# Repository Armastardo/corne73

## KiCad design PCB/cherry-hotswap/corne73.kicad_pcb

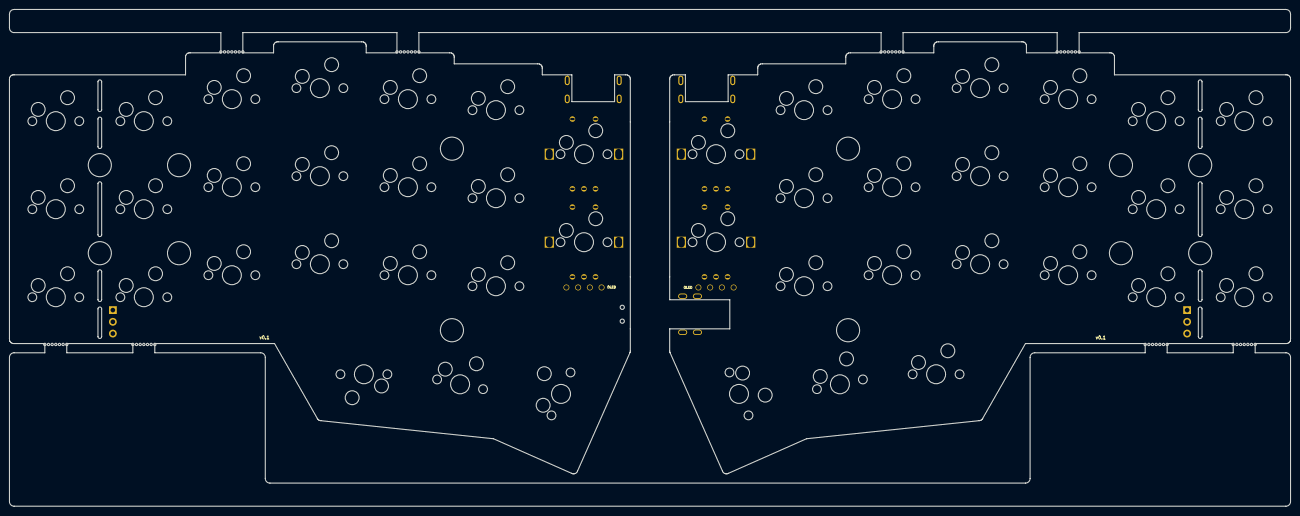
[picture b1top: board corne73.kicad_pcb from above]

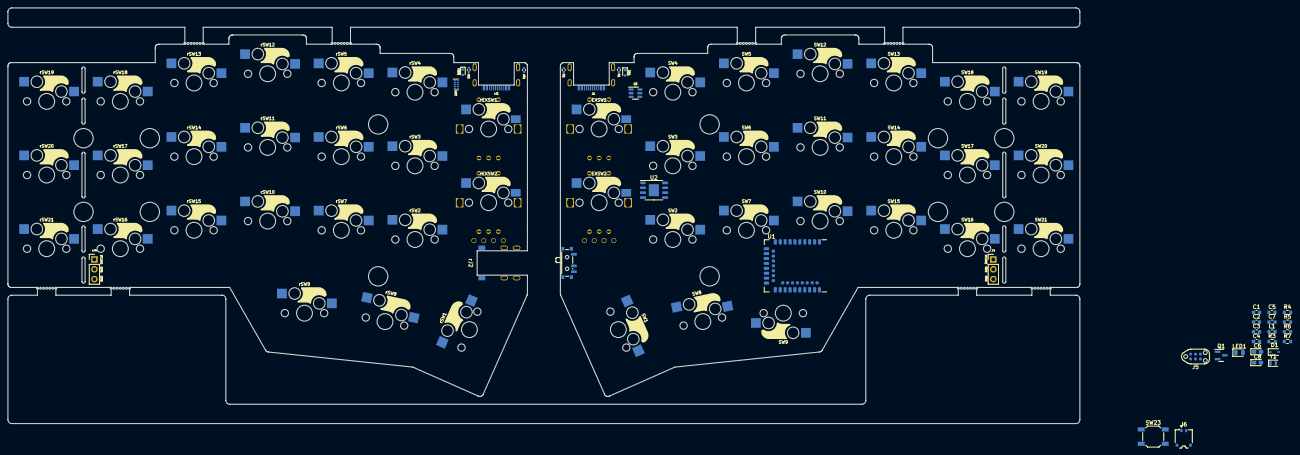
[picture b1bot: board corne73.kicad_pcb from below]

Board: 2 copper layers, 277.2 x 107.5 mm, 101 parts (87 on the bottom side), 31 nets, no tracks yet.

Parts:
BT1, BT2, BT3, BT4: Breakaway Tabs; Breakaway_Tabs
C1, C2: 12p; C_0603_1608Metric
C3, C5, C7: 4.7u; C_0603_1608Metric
C4: 1u; C_0603_1608Metric
C6, C8: 10uF; CP_EIA-2012-12_Kemet-R
D1: Schottky; D_SOD-323
EXSW1, EXSW2: RotaryEncoder_Switch; keyswitch_cherrymx_hotswap_1u_rotary_encoder_ec12
H1, H2, H3, H4: qw-logo; qw new logo silk + copper sm
H5, H6, H7, H8: 1999-logo; 1999 logo md
J1: TYPE-C-31-M-13C
J3: Conn_01x04; OLED
J4: Conn_01x03; PinHeader_1x03_P2.54mm_Vertical
J5: TC2030_SWD; CON_TC2030_outlined
J6: Battery; Molex_Pico-EZmate_78171-0002_1x02-1MP_P1.20mm_Vertical
L1: 10 uH; L_0603_1608Metric
LED1: CHARGE; LED_0805_2012Metric
Q1: AO3401A; SOT-23
R1, R2: 5.1k; R_0402_1005Metric
R3: 806; R_0603_1608Metric
R4: 2M; R_0603_1608Metric
R5: 10k; R_0603_1608Metric
R6, R7: 5k; R_0603_1608Metric
SW1: SW_Push; keyswitch_cherrymx_hotswap_1.5u
SW2, SW3, SW4, SW5, SW6, SW7, SW8, SW9, SW10, SW11, SW12, SW13, SW14, SW15, SW16, SW17, SW18, SW19, SW20, SW21: SW_Push; keyswitch_cherrymx_hotswap_1u
SW22: SW_SPDT; SW_SPDT_PCM12
SW23: SW_Push; SW_SPST_SKQG_WithStem
U1: nRF52840_E73-2G4M08S1C
U2: TP4056; CustomTP4056
U3: USBLC6-2SC6; SOT-23-6
Y1: 32.768 KHz; Crystal_SMD_2012-2Pin_2.0x1.2mm
ZD1: RB521S30T1G; D_SOD-523
rBT1, rBT2, rBT3, rBT4: Breakaway Tabs; Breakaway_Tabs
rEXSW1, rEXSW2: RotaryEncoder_Switch; keyswitch_cherrymx_hotswap_1u_rotary_encoder_ec12
rJ1: TYPE-C-31-M-13C
rJ2: TRS; PJ-398A-5A_PJ-399B-6A
rJ3: Conn_01x04; OLED
rJ4: Conn_01x03; PinHeader_1x03_P2.54mm_Vertical
rR1, rR2: 5.1k; R_0402_1005Metric
rSW1: SW_Push; keyswitch_cherrymx_hotswap_1.5u
rSW2, rSW3, rSW4, rSW5, rSW6, rSW7, rSW8, rSW9, rSW10, rSW11, rSW12, rSW13, rSW14, rSW15, rSW16, rSW17, rSW18, rSW19, rSW20, rSW21: SW_Push; keyswitch_cherrymx_hotswap_1u
rU3: TPD4E05U06DQAR; USON-10_2.5x1.0mm_P0.5mm
rZD1: RB521S30T1G; D_SOD-523

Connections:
+5V: C3.1, C6.1, C7.1, D1.2 (A), J3.3, LED1.2 (A), Q1.1 (G), R6.1, U1.27 (VBUS), U2.4 (VCC), U2.8 (CE), U3.5 (VBUS), ZD1.1 (K)
+5VR: rJ2.T, rJ3.3, rZD1.1 (K)
+BATT: C8.1, J6.2, R3.1, U2.5 (BAT)
+VSW: C5.1, D1.1 (K), Q1.2 (S), U1.23 (VDDH)
/left/REB: EXSW1.B, EXSW2.B
/right/D+: rJ1.A6 (D+), rJ1.B6 (D+), rU3.1 (D1+), rU3.4 (D2+), rU3.7 (NC), rU3.10 (NC)
/right/D-: rJ1.A7 (D-), rJ1.B7 (D-), rU3.2 (D1-), rU3.5 (D2-), rU3.6 (NC), rU3.9 (NC)
/right/REB: rEXSW1.B, rEXSW2.B
D+: U1.31 (D+), U3.4 (I/O2)
D-: U1.29 (D-), U3.3 (I/O2)
DBUS+: J1.A6 (D+), J1.B6 (D+), U3.6 (I/O1)
DBUS-: J1.A7 (D-), J1.B7 (D-), U3.1 (I/O1)
DCCH: L1.1, U1.25 (DCCH)
GND: C1.2, C2.2, C3.2, C4.2, C5.2, C6.2, C7.2, C8.2, EXSW1.C, EXSW1.S1, EXSW2.C, EXSW2.S1, J1.A1 (GND), J1.A12 (GND), J1.B1 (GND), J1.B12 (GND), J1.S1 (SHIELD), J3.4, J4.2, J5.5 (GND), J6.1, J6.MP (MountPin), R1.1, R2.1, R4.2, R6.2, R7.2, SW1.2, SW2.2, SW3.2, SW4.2, SW5.2, SW6.2, SW7.2, SW8.2, SW9.2, SW10.2, SW11.2, SW12.2, SW13.2, SW14.2, SW15.2, SW16.2, SW17.2, SW18.2, SW19.2, SW20.2, SW21.2, U1.5 (GND), U1.21 (GND), U1.24 (GND), U2.1 (TEMP), U2.3 (GND), U3.2 (GND)
GNDR: rEXSW1.C, rEXSW1.S1, rEXSW2.C, rEXSW2.S1, rJ1.A1 (GND), rJ1.A12 (GND), rJ1.B1 (GND), rJ1.B12 (GND), rJ1.S1 (SHIELD), rJ2.S, rJ3.4, rJ4.2, rR1.1, rR2.1, rSW1.2, rSW2.2, rSW3.2, rSW4.2, rSW5.2, rSW6.2, rSW7.2, rSW8.2, rSW9.2, rSW10.2, rSW11.2, rSW12.2, rSW13.2, rSW14.2, rSW15.2, rSW16.2, rSW17.2, rSW18.2, rSW19.2, rSW20.2, rSW21.2, rU3.3 (GND), rU3.8 (GND)
unnamed: J1.A5 (CC1), R1.2
unnamed: J1.B5 (CC2), R2.2
unnamed: LED1.1 (K), R5.1
unnamed: C1.1, U1.11 (P0.00/XL1), Y1.2
unnamed: C2.1, U1.13 (P0.01/XL2), Y1.1
unnamed: R5.2, U2.7 (CHRG)
unnamed: R7.1, U2.2 (PROG)
unnamed: rJ1.A5 (CC1), rR1.2
unnamed: rJ1.B5 (CC2), rR2.2
RESET: J5.3 (~RST), U1.26 (P0.18/~RESET)
SWDCLK: J5.4 (SWCLK), U1.39 (SWDCLK)
SWDIO: J5.2 (SWDIO), U1.37 (SWDIO)
VBUS: J1.A4 (VBUS), J1.A9 (VBUS), J1.B4 (VBUS), J1.B9 (VBUS), ZD1.2 (A)
VBUSR: rJ1.A4 (VBUS), rJ1.A9 (VBUS), rJ1.B4 (VBUS), rJ1.B9 (VBUS), rZD1.2 (A)
VDD: C4.1, J5.1 (VCC), L1.2, U1.19 (VDD)
VSENSE: R3.2, R4.1, U1.15 (P0.05/AIN3)

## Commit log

2024-07-06 Adjusted license and gitignore
2024-07-06 Copied crkbd cherry-hotswap over
2024-07-07 Removed unused electronics
2024-07-07 Initial left side components
